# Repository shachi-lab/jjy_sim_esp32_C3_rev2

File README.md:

# JJY-SIM Rev.2 (JJY Time Signal Simulator for ESP32-C3)

[🇯🇵 日本語版はこちら](README_ja.md)

**JJY-SIM** is a compact time signal simulator that emulates Japan's JJY standard radio time code (40 kHz / 60 kHz) using an ESP32-C3 and the Arduino framework.  
It fetches accurate NTP time and generates a modulated JJY signal via PWM. 
**Rev.2** introduces an H-bridge RF output for higher transmission power and improved stability.

<br/>

---

## 🪛 Features

- Compact design using **ESP32-C3 + Arduino**  
- Easy Wi-Fi setup with single-button **AP mode**  
- **OLED display** shows current time and sync status  
- Automatic time synchronization via **NTP**  
- Switchable **JJY 40 kHz (East Japan) / 60 kHz (West Japan)** output  
- Signal transmitted from a built-in **mini antenna** on the board  
- **H-bridge driver** provides high output power (⚠ may transmit farther than expected)  
- Configurable through a **web browser setup page**  
- Supports **local time zones (UTC offset)** and **DST (Daylight Saving Time)**

---

## ⚙️ How to Build

1. **Set up ESP32 boards in Arduino IDE**
   - Boards Manager URL:  
     `https://dl.espressif.com/dl/package_esp32_index.json`
   - Target board: **ESP32-C3 Dev Module**

2. **Install required libraries**
   - [WiFiManager](https://github.com/tzapu/WiFiManager)（v2.0.17 recommended）
   - [ESP8266 and ESP32 OLED driver for SSD1306 displays](https://github.com/ThingPulse/esp8266-oled-ssd1306) (v4.6.0 recommended)

3. **Open the sketch**
   - File: `JJY_Sim_ESP32_C3_REV2.ino`

4. **Compile and upload**
   - Select the correct board and COM port.
   - Click “Upload”.

> 💡 **Note:**  
ESP32-C3 uses its built-in **native USB-UART** for flashing and serial communication.  
On Windows, you may need the official **Espressif USB driver**:  
[Download here](https://www.espressif.com/en/support/download/other-tools)

> ⚠️ **First Boot:**  
During the first startup immediately after writing the program, the system builds a file system in the internal flash memory. Because of this, there may be no response for several tens of seconds, making it appear as if the system has “hung.”
Once the process is complete, the system will automatically reboot, and from then on it will start up normally. If it does not reboot automatically, please press the RESET button to restart.

---

## 📶 Wi-Fi Setup

- After power-on or reset, press the **CONFIG** switch within 5 seconds.  
- An AP named `ESP32_XXXXXXXX` starts (password: `password`).  
- Connect from your phone or PC → captive portal.
- [WiFi Configure] page → set your Wi-Fi SSID and password. 
- [Setup] page allows configuration of BAND, local time, and DST settings.

---

## 🕒 Operation

- If no button is pressed, the device connects to your Wi-Fi automatically.  
- Retrieves time from NTP server.  
- Displays current time on OLED.  
- Starts PWM JJY signal output synchronized to the next 0 second.  
- Place your radio-controlled clock near the antenna and press its “Receive” button.

---

## 🔌 Pin Assignments

| Function | GPIO | Description |
|-----------|------|-------------|
| JJY PWM Output | 10, 4 | Modulated signal (A/B for H-bridge) |
| CONFIG Switch | 9 | Wi-Fi setup (shared with BOOT) |
| ACT LED | 5 | Activity indicator |
| IND LED | 0 | Status indicator |
| OLED Reset | 2 | OLED hardware reset |
| OLED SDA | 7 | I²C data |
| OLED SCL | 6 | I²C clock |

---

## 🧾 File Structure

All Arduino source files are in the **`Source/`** folder:

```
JJY_Sim_ESP32_C3_REV2.ino   // Main sketch
wire_compat.h               // I²C compatibility header for ESP32-C3
shachi-lab_logo.h           // Logo bitmap
src/WiFiManager/            // Several files in this folder
```

---

## 📚 Dependencies

- [ESP8266 and ESP32 OLED driver for SSD1306 displays](https://github.com/ThingPulse/esp8266-oled-ssd1306)

---

## 🧰 Hardware Data

KiCad design files are included in the **`KiCad/`** folder.  
- Compatible with **KiCad v9** (older versions not supported)  
- **Gerber files** for fabrication are located in `KiCad/PLOT/`.

---

## ⚠️ Legal Notice

This device emits real low-frequency RF signals.  
Please use it responsibly and ensure compliance with local radio regulations.

---

## 🔗 Related Links

- Blog article (Japanese, detailed build notes):  
  👉 https://blog.shachi-lab.com/047_jjy_sim_rev2/

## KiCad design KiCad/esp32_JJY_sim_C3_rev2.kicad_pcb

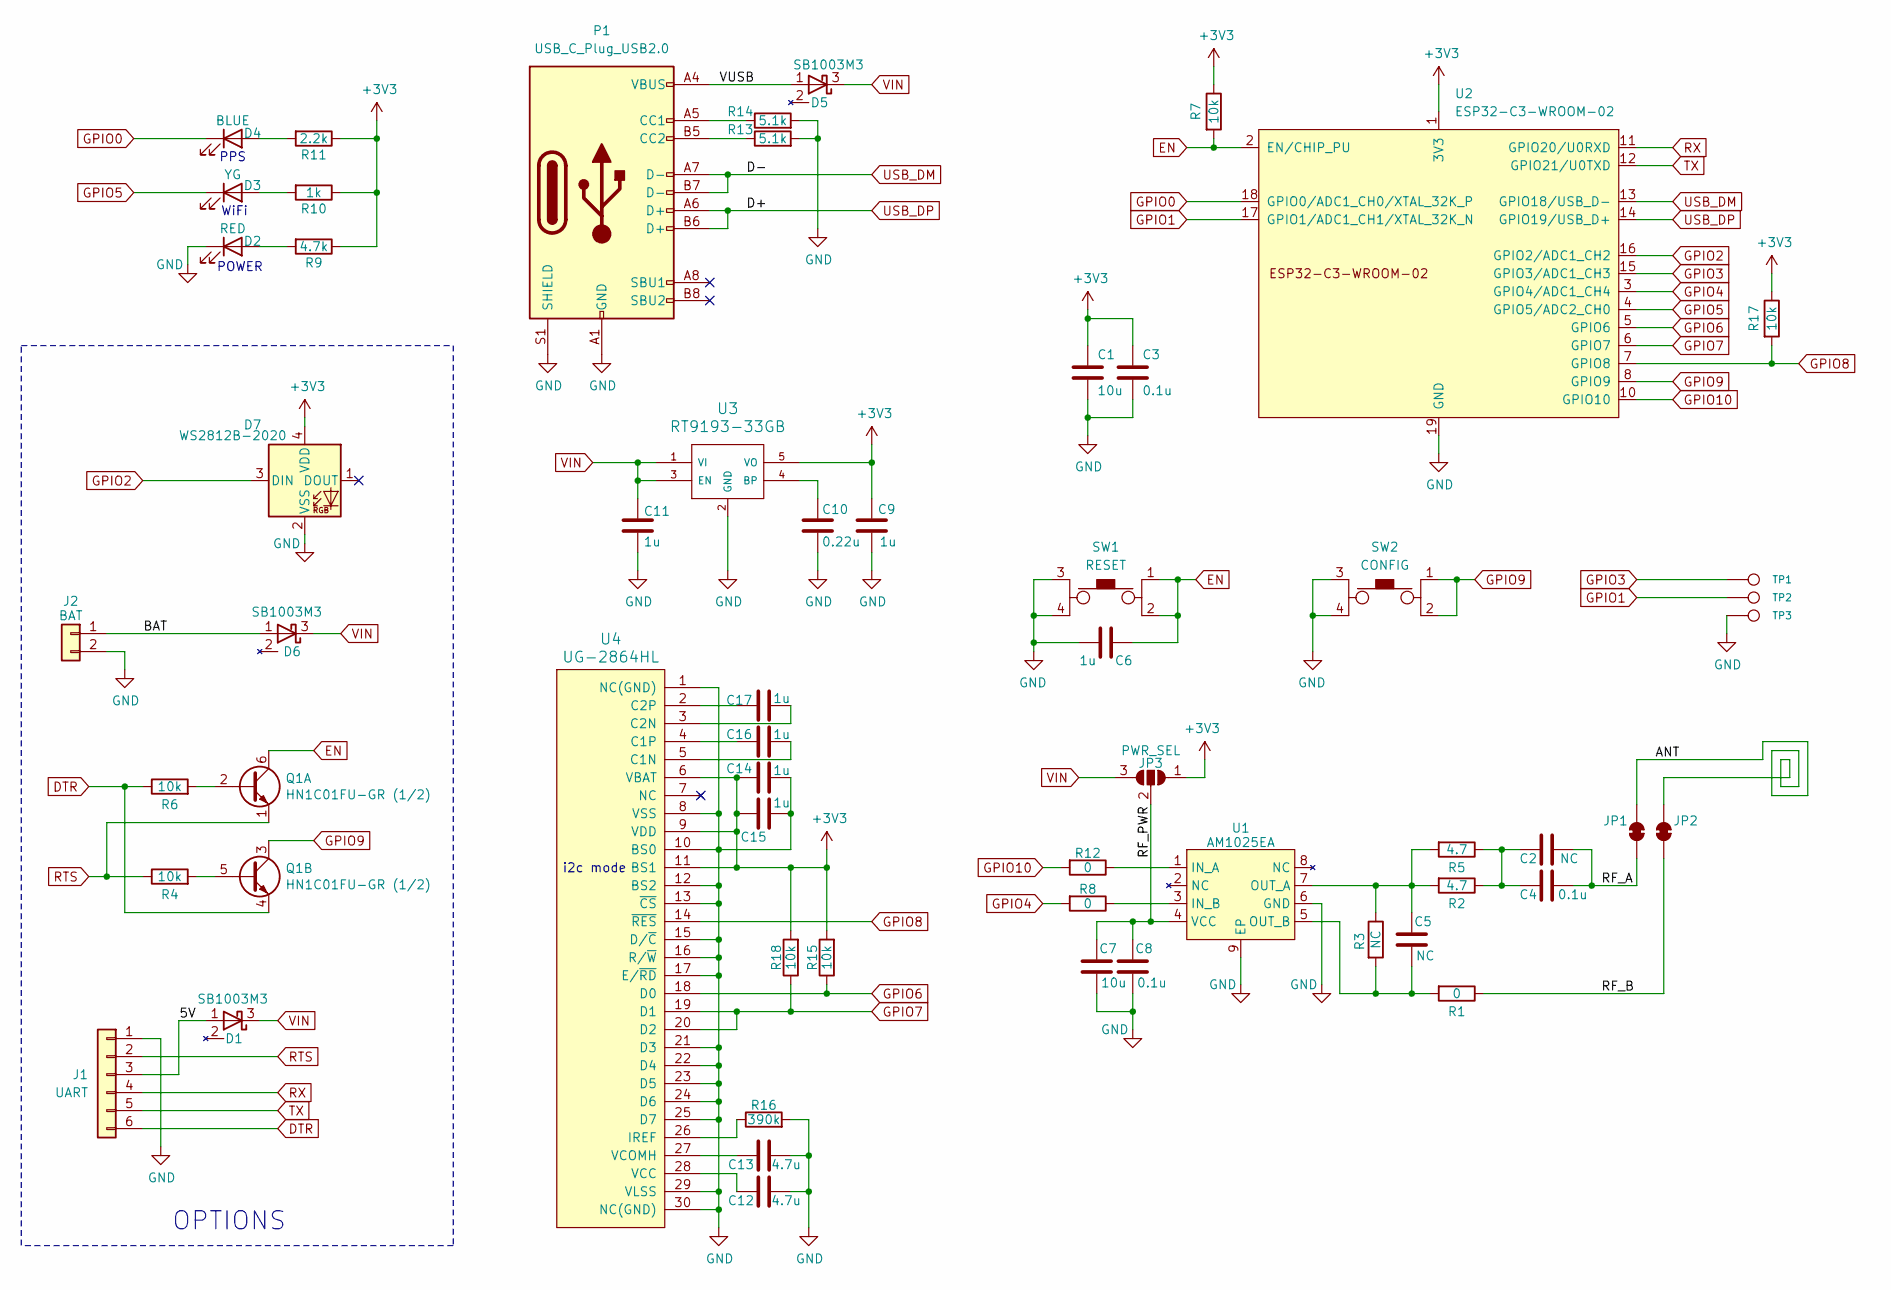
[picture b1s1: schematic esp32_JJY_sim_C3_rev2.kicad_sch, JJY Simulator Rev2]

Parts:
C1, C7: 10u; C_0603_1608Metric
C2, C5: NC; C_0603_1608Metric
C3, C4, C8: 0.1u; C_0603_1608Metric
C6, C9, C11, C14, C15, C16, C17: 1u; C_0603_1608Metric
C10: 0.22u; C_0603_1608Metric
C12, C13: 4.7u; C_0603_1608Metric
D1, D5, D6: SB1003M3; SOT-323_SC-70
D2: RED; LED_0603_1608Metric
D3: YG; LED_0603_1608Metric
D4: BLUE; LED_0603_1608Metric
D7: WS2812B-2020; LED_WS2812B-2020_PLCC4_2.0x2.0mm
J1: UART; PinHeader_1x06_P2.54mm_Horizontal
J2: BAT; JST_ZH_S2B-ZR_02x1.5mm_Angled
JP1: ANT-A; Jumper-2_TH_3.81mm
JP2: GND; Jumper-2_TH_3.81mm
JP3: PWR_SEL; SolderJumper-3_P1.3mm_Open_RoundedPad1.0x1.5mm_NumberLabels
P1: USB_C_Plug_USB2.0; 5077CR-16SMC2-BK-TR
Q1: HN1C01FU-GR (1/2); 2-2J1A
R1, R8, R12: 0; R_0603_1608Metric
R2, R5: 4.7; R_0603_1608Metric
R3: NC; R_0603_1608Metric
R4, R6, R7, R15, R17, R18: 10k; R_0603_1608Metric
R9: 4.7k; R_0603_1608Metric
R10: 1k; R_0603_1608Metric
R11: 2.2k; R_0603_1608Metric
R13, R14: 5.1k; R_0603_1608Metric
R16: 390k; R_0603_1608Metric
SW1: RESET; SKRPACE010
SW2: CONFIG; SKRPACE010
TP1, TP2, TP3: TP; TestPoint_THTPad_D1.5mm_Drill0.7mm
U1: AM1025EA; eSOP-8_3.9x5.05mm_EP_3.1x2.2mm_P1.27mm
U2: ESP32-C3-WROOM-02
U3: RT9193-33GB; SOT-23-5
U4: UG-2864HL; UG-2864-FPC

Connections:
+3V3: C1.1, C3.1, C9.1, C14.1, C15.1, D7.4 (VDD), JP3.1 (A), R7.1, R9.1, R10.1, R11.1, R15.2, R17.1, R18.2, U2.1 (3V3), U3.5 (VO), U4.6 (VBAT), U4.9 (VDD), U4.11 (BS1)
/5V: D1.1 (A), J1.3
/ANT: JP1.2 (B), JP2.2 (B)
/BAT: D6.1 (A), J2.1
/RF_A: C2.2, C4.2, JP1.1 (A)
/RF_B: JP2.1 (A), R1.1
/RF_PWR: C7.1, C8.1, JP3.2 (C), U1.4 (VCC)
/VUSB: D5.1 (A), P1.A4 (VBUS), P1.A9 (VBUS), P1.B4 (VBUS), P1.B9 (VBUS)
DTR: J1.6, Q1.4 (E2), R6.1
EN: C6.2, Q1.6 (C1), R7.2, SW1.1, SW1.2, U2.2 (EN/CHIP_PU)
GND: C1.2, C3.2, C6.1, C7.2, C8.2, C9.2, C10.2, C11.2, C12.2, C13.2, C14.2, C15.2, D2.1 (K), D7.2 (VSS), J1.1, J2.2, P1.A1 (GND), P1.A12 (GND), P1.B1 (GND), P1.B12 (GND), P1.S1 (SHIELD), R13.2, R14.2, R16.2, SW1.3, SW1.4, SW2.3, SW2.4, TP3.1, U1.6 (GND), U1.9 (EP), U2.9 (GND), U2.19 (GND), U3.2 (GND), U4.1 (N.C.), U4.8 (VSS), U4.10 (BS0), U4.12 (BS2), U4.13 (~CS), U4.15 (D/~C), U4.16 (R/~W), U4.17 (E/~RD), U4.21 (D3), U4.22 (D4), U4.23 (D5), U4.24 (D6), U4.25 (D7), U4.29 (VLSS), U4.30 (N.C.)
GPIO0: D4.1 (K), U2.18 (GPIO0/ADC1_CH0/XTAL_32K_P)
GPIO1: TP2.1, U2.17 (GPIO1/ADC1_CH1/XTAL_32K_N)
GPIO2: D7.3 (DIN), U2.16 (GPIO2/ADC1_CH2)
GPIO3: TP1.1, U2.15 (GPIO3/ADC1_CH3)
GPIO4: R8.2, U2.3 (GPIO4/ADC1_CH4)
GPIO5: D3.1 (K), U2.4 (GPIO5/ADC2_CH0)
GPIO6: R15.1, U2.5 (GPIO6), U4.18 (D0)
GPIO7: R18.1, U2.6 (GPIO7), U4.19 (D1), U4.20 (D2)
GPIO8: R17.2, U2.7 (GPIO8), U4.14 (~RES)
GPIO9: Q1.3 (C2), SW2.1, SW2.2, U2.8 (GPIO9)
GPIO10: R12.2, U2.10 (GPIO10)
unnamed: C2.1, C4.1, R2.1, R5.1
unnamed: D2.2 (A), R9.2
unnamed: D3.2 (A), R10.2
unnamed: D4.2 (A), R11.2
unnamed: P1.A5 (CC1), R14.1
unnamed: P1.B5 (CC2), R13.1
unnamed: Q1.2 (B1), R6.2
unnamed: Q1.5 (B2), R4.2
unnamed: R12.1, U1.1 (IN_A)
unnamed: R8.1, U1.3 (IN_B)
unnamed: C5.1, R2.2, R3.1, R5.2, U1.7 (OUT_A)
unnamed: C5.2, R1.2, R3.2, U1.5 (OUT_B)
unnamed: C10.1, U3.4 (BP)
unnamed: C16.2, U4.5 (C1N)
unnamed: C16.1, U4.4 (C1P)
unnamed: C17.2, U4.3 (C2N)
unnamed: C17.1, U4.2 (C2P)
unnamed: R16.1, U4.26 (IREF)
unnamed: C12.1, U4.28 (VCC)
unnamed: C13.1, U4.27 (VCOMH)
RTS: J1.2, Q1.1 (E1), R4.1
RX: J1.4, U2.11 (GPIO20/U0RXD)
TX: J1.5, U2.12 (GPIO21/U0TXD)
USB_DM: P1.A7 (D-), P1.B7 (D-), U2.13 (GPIO18/USB_D-)
USB_DP: P1.A6 (D+), P1.B6 (D+), U2.14 (GPIO19/USB_D+)
VIN: C11.1, D1.3 (K), D5.3 (K), D6.3 (K), JP3.3 (B), U3.1 (VI), U3.3 (EN)

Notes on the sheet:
OPTIONS
PPS
i2c mode
WiFi
POWER

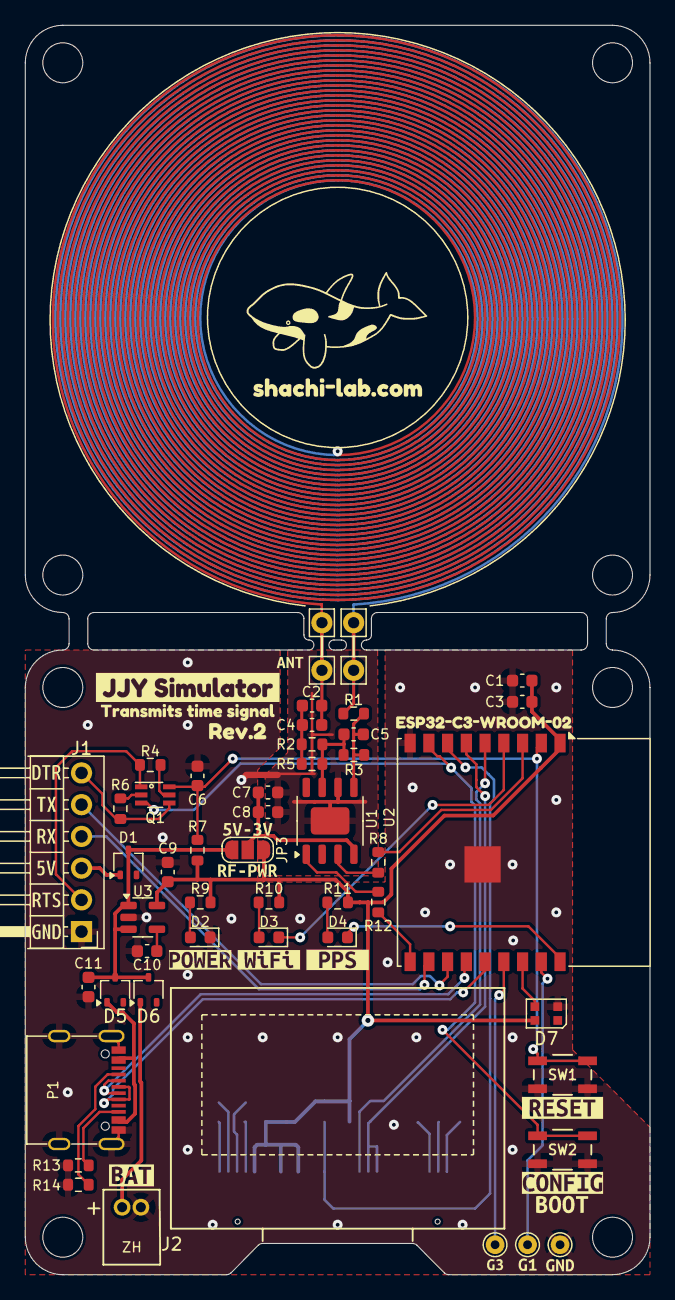
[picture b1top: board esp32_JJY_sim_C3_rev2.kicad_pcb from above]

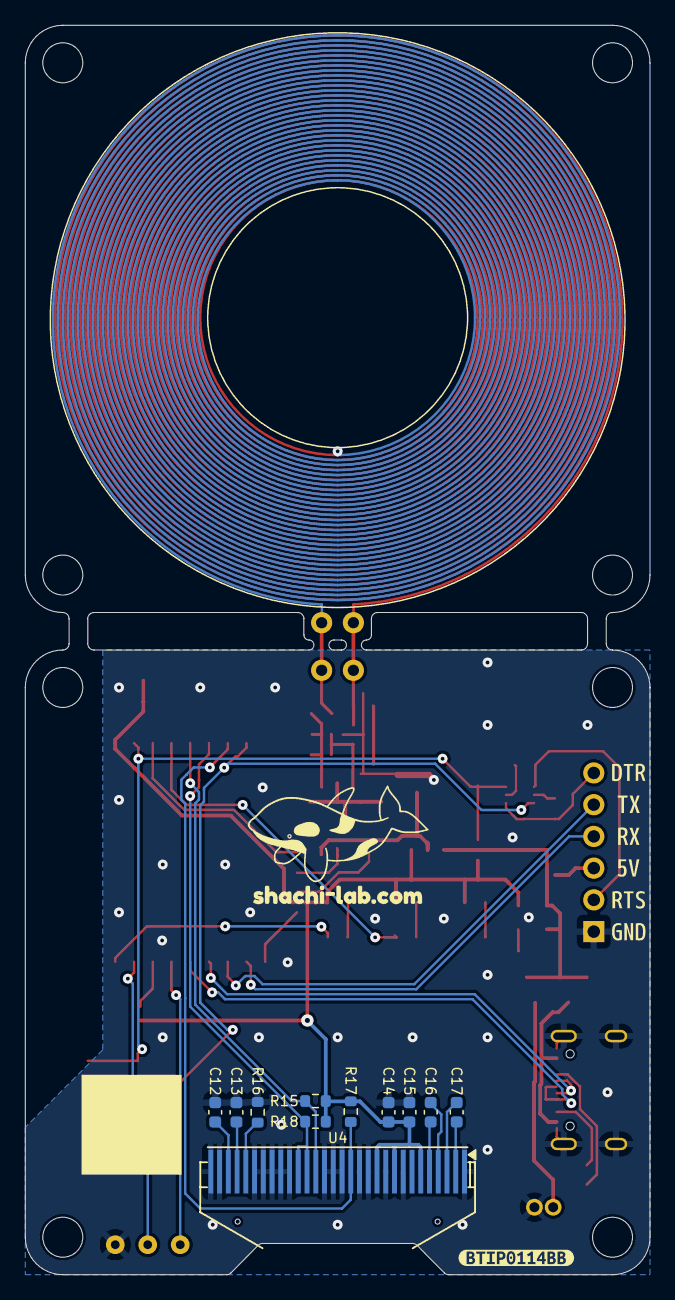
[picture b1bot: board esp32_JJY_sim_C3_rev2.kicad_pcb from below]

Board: 2 copper layers, 50.0 x 100.0 mm, 90 parts (19 on the bottom side), 48 nets.

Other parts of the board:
kibuzzard-1: G***; kibuzzard-6646C6AC
kibuzzard-4: G***; kibuzzard-66603A24
kibuzzard-5: G***; kibuzzard-68C580B0
kibuzzard-6: G***; kibuzzard-665BB8B1
kibuzzard-7: G***; kibuzzard-665BB8AA
kibuzzard-8: G***; kibuzzard-68D324C9
kibuzzard-9: G***; kibuzzard-665BB8A3
kibuzzard-10: G***; kibuzzard-665BB89D
kibuzzard-11: G***; kibuzzard-68D324EE
kibuzzard-12: G***; kibuzzard-669B8438
kibuzzard-13: G***; kibuzzard-665BB88E
kibuzzard-14: G***; kibuzzard-669B6BC9
kibuzzard-15: G***; kibuzzard-669B6DC4
kibuzzard-17: G***; kibuzzard-665B3587
kibuzzard-18: G***; kibuzzard-665B35C9
kibuzzard-19: G***; kibuzzard-665B357F
kibuzzard-20: G***; kibuzzard-669B16B9
kibuzzard-21: G***; kibuzzard-665A8DD6
kibuzzard-22: G***; kibuzzard-669B4532
kibuzzard-23: G***; kibuzzard-665B35AE
kibuzzard-24: G***; kibuzzard-665BBA5E
kibuzzard-25: G***; kibuzzard-665BBA64
kibuzzard-26: G***; kibuzzard-665BBA69
kibuzzard-27: G***; kibuzzard-665BBA6E
kibuzzard-28, kibuzzard-28#2: G***; kibuzzard-68D2B4BB
kibuzzard-29: G***; kibuzzard-669B8430
kibuzzard-30: G***; kibuzzard-665BBA79
kibuzzard-68D3A9C1: G***; kibuzzard-68D3A9C1
kibuzzard-68D3A910: G***; kibuzzard-68D3A910
kibuzzard-68DDC93A: G***; kibuzzard-68DDC93A
kibuzzard-68E061D7: G***; kibuzzard-68E061D7

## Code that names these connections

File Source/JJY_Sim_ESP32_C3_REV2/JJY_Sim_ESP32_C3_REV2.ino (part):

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#define FORMAT_SPIFFS_IF_FAILED true

#undef  BUILTIN_LED
#define BUILTIN_LED       0       // GPIO0
#define PIN_LED_WAVE      BUILTIN_LED
#define PIN_LED_WIFI      5       // GPIO5
#define PIN_CONFIG        9       // GPIO9
#define PIN_OLED_RES      8       // GPIO8
#define PIN_OLED_SCL      6       // GPIO6
#define PIN_OLED_SDA      7       // GPIO7
#define PIN_PWM_A         10      // GPIO10
#define PIN_PWM_B         4       // GPIO4

#define OLED_I2CADR       0x3c

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
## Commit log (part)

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2025-11-04 1st commit
2025-11-04 Added Gerber data files
2025-11-04 Revise README for improved clarity and details
    Updated README.md for clarity and additional information.
2025-11-10 Fix minor bugs and add Shachi-lab logo display
2025-11-10 Switch to English README as main
    - Set English README.md as the default main document
    - Moved Japanese version to README_ja.md
    - Updated internal links
2025-11-12 Add timezone and DST support
    - Web-configurable UTC offset and DST flag
    - Updated NTP sync handling
    - Display now shows UTC+offset and DST indicator
    - Using in-repo customized WiFiManager
2025-11-12 bug fix
2025-11-12 Updated product image for the latest revision
2025-11-12 README correction
2025-11-14 remove custom WiFiManager and update main source
2026-01-25 add 3DPrint
2026-01-26 3DPrintを変更 - Topに不透明用を追加 - Bottomにロゴ追加
